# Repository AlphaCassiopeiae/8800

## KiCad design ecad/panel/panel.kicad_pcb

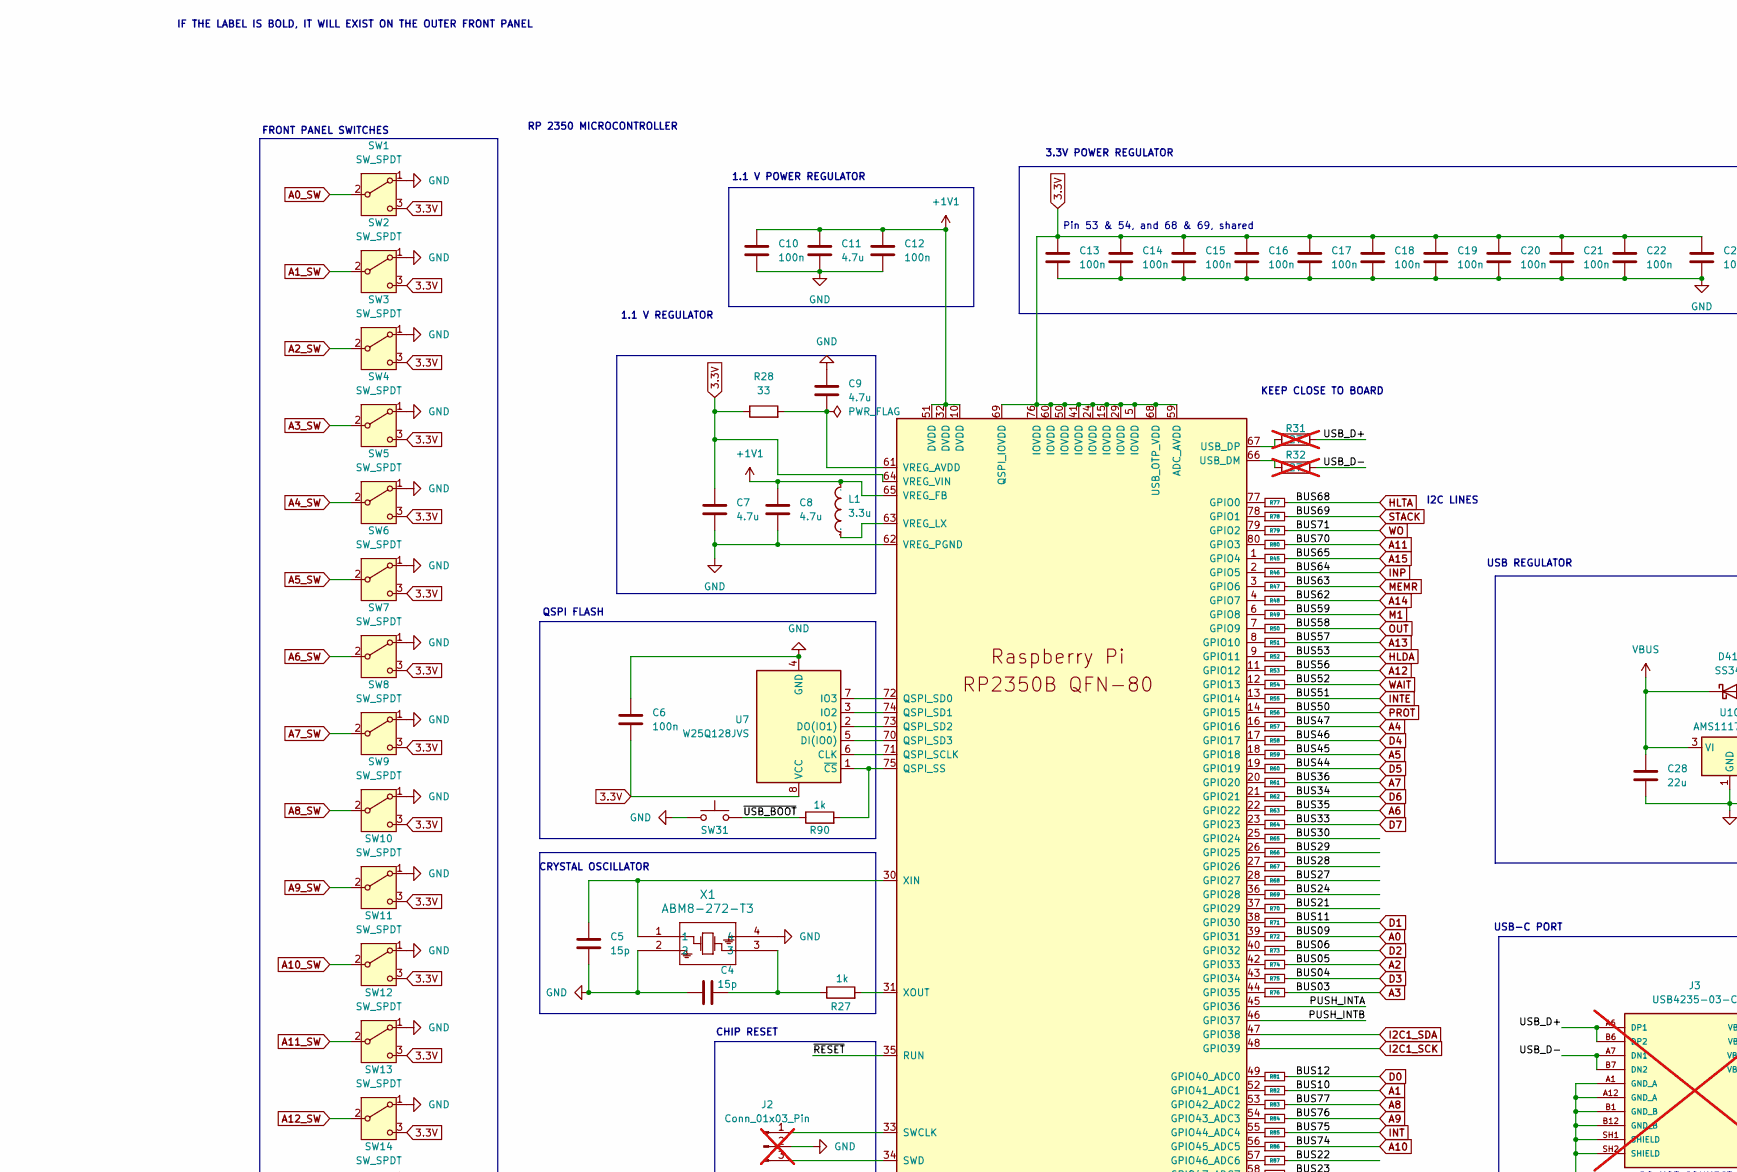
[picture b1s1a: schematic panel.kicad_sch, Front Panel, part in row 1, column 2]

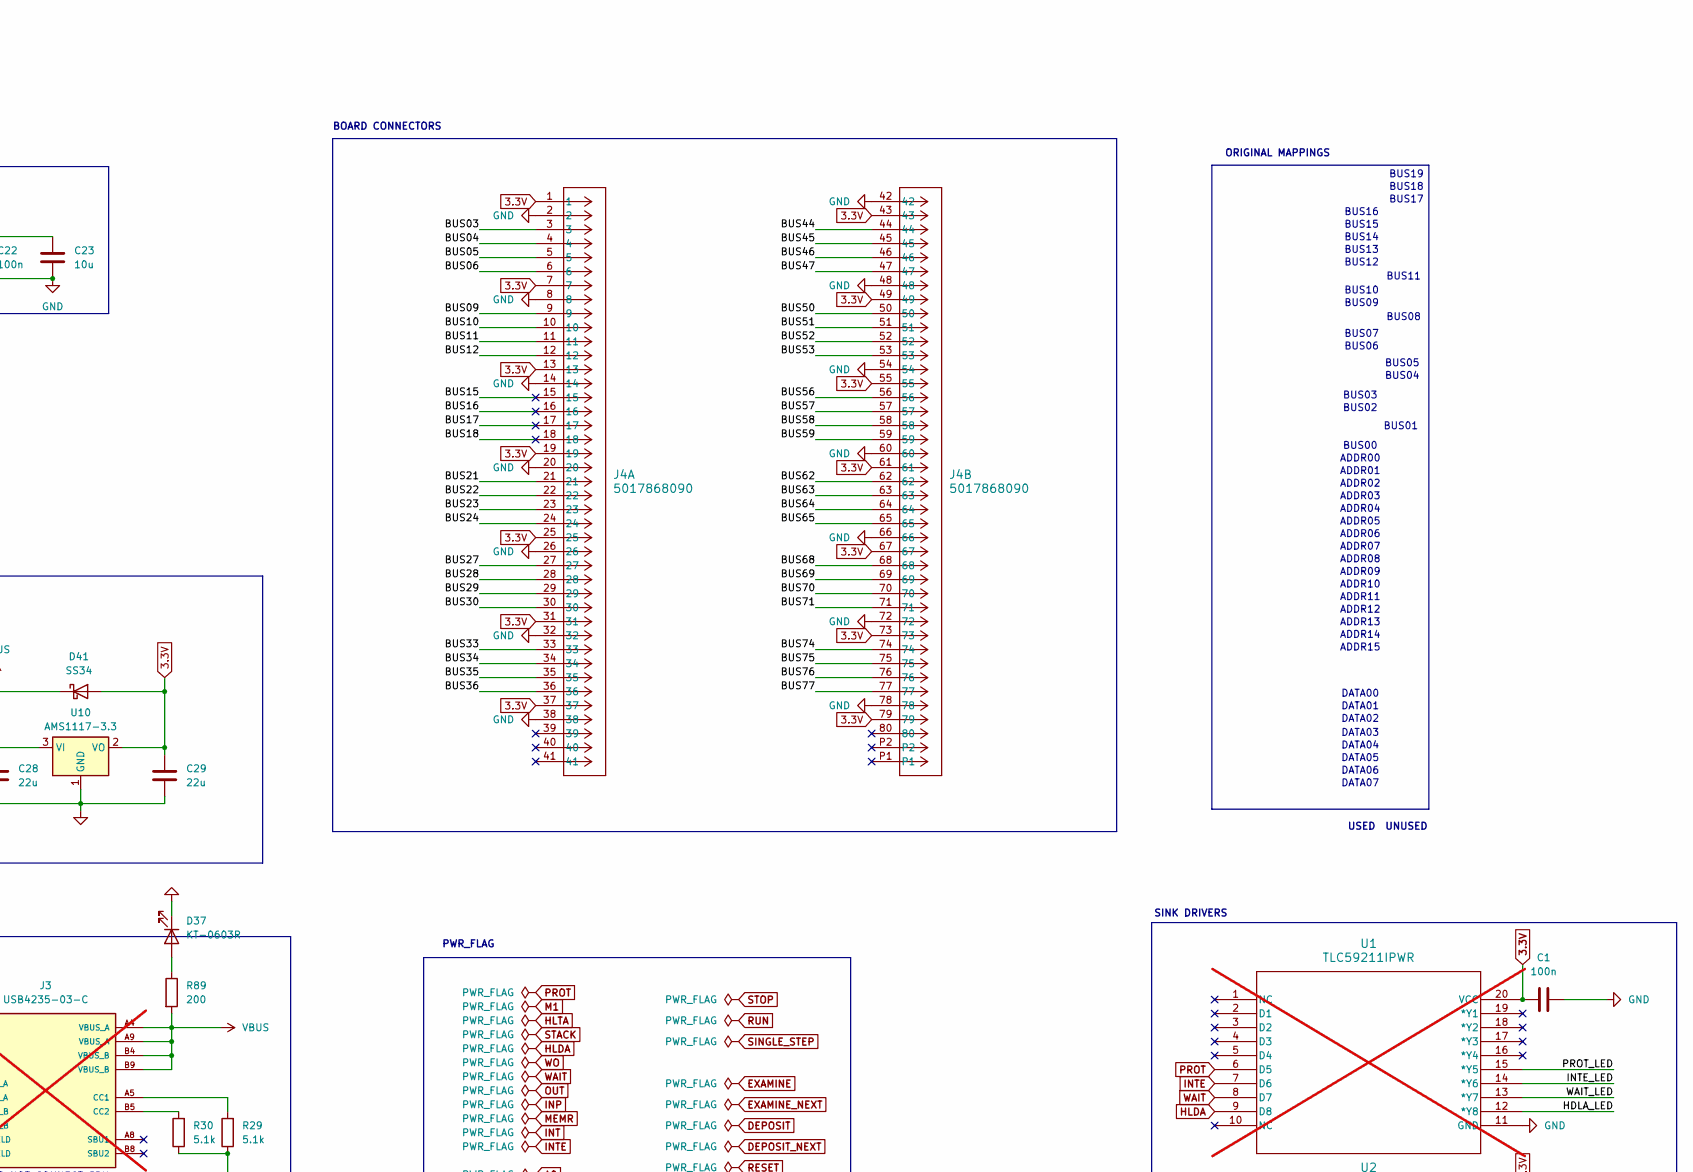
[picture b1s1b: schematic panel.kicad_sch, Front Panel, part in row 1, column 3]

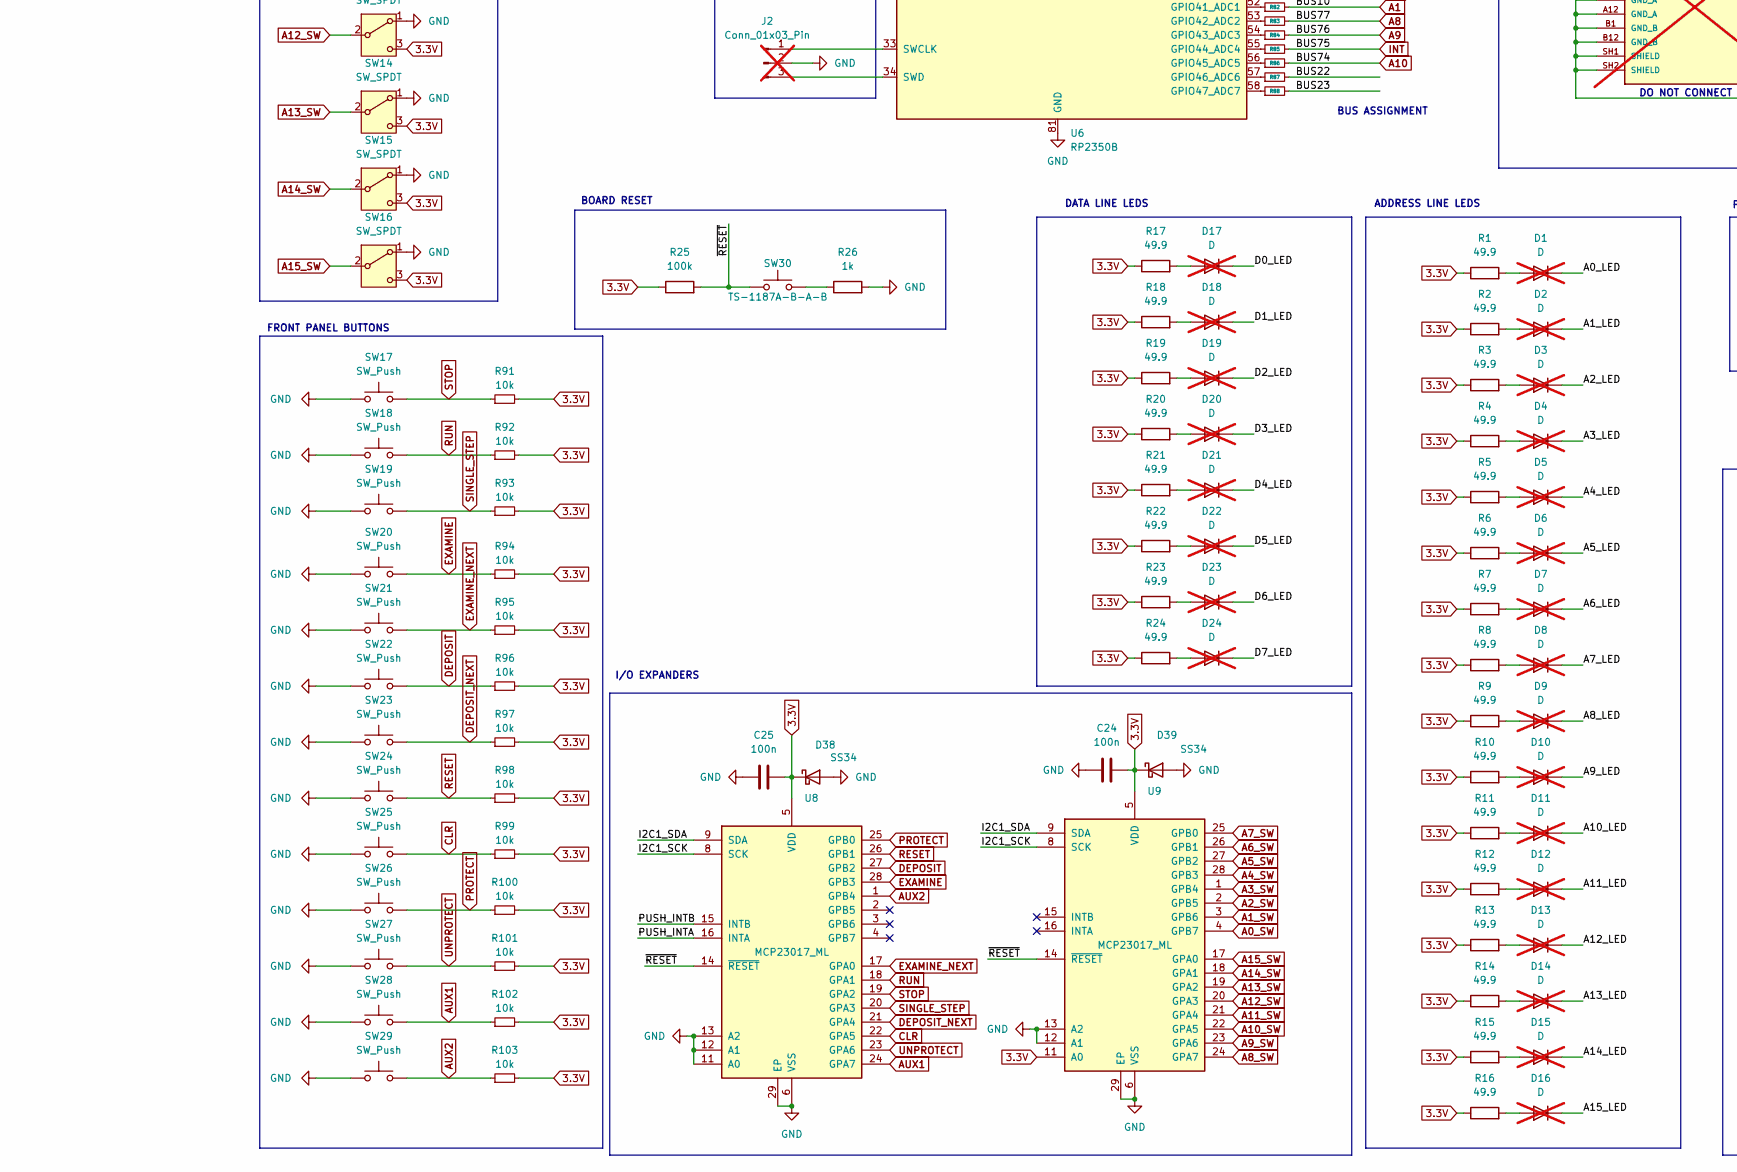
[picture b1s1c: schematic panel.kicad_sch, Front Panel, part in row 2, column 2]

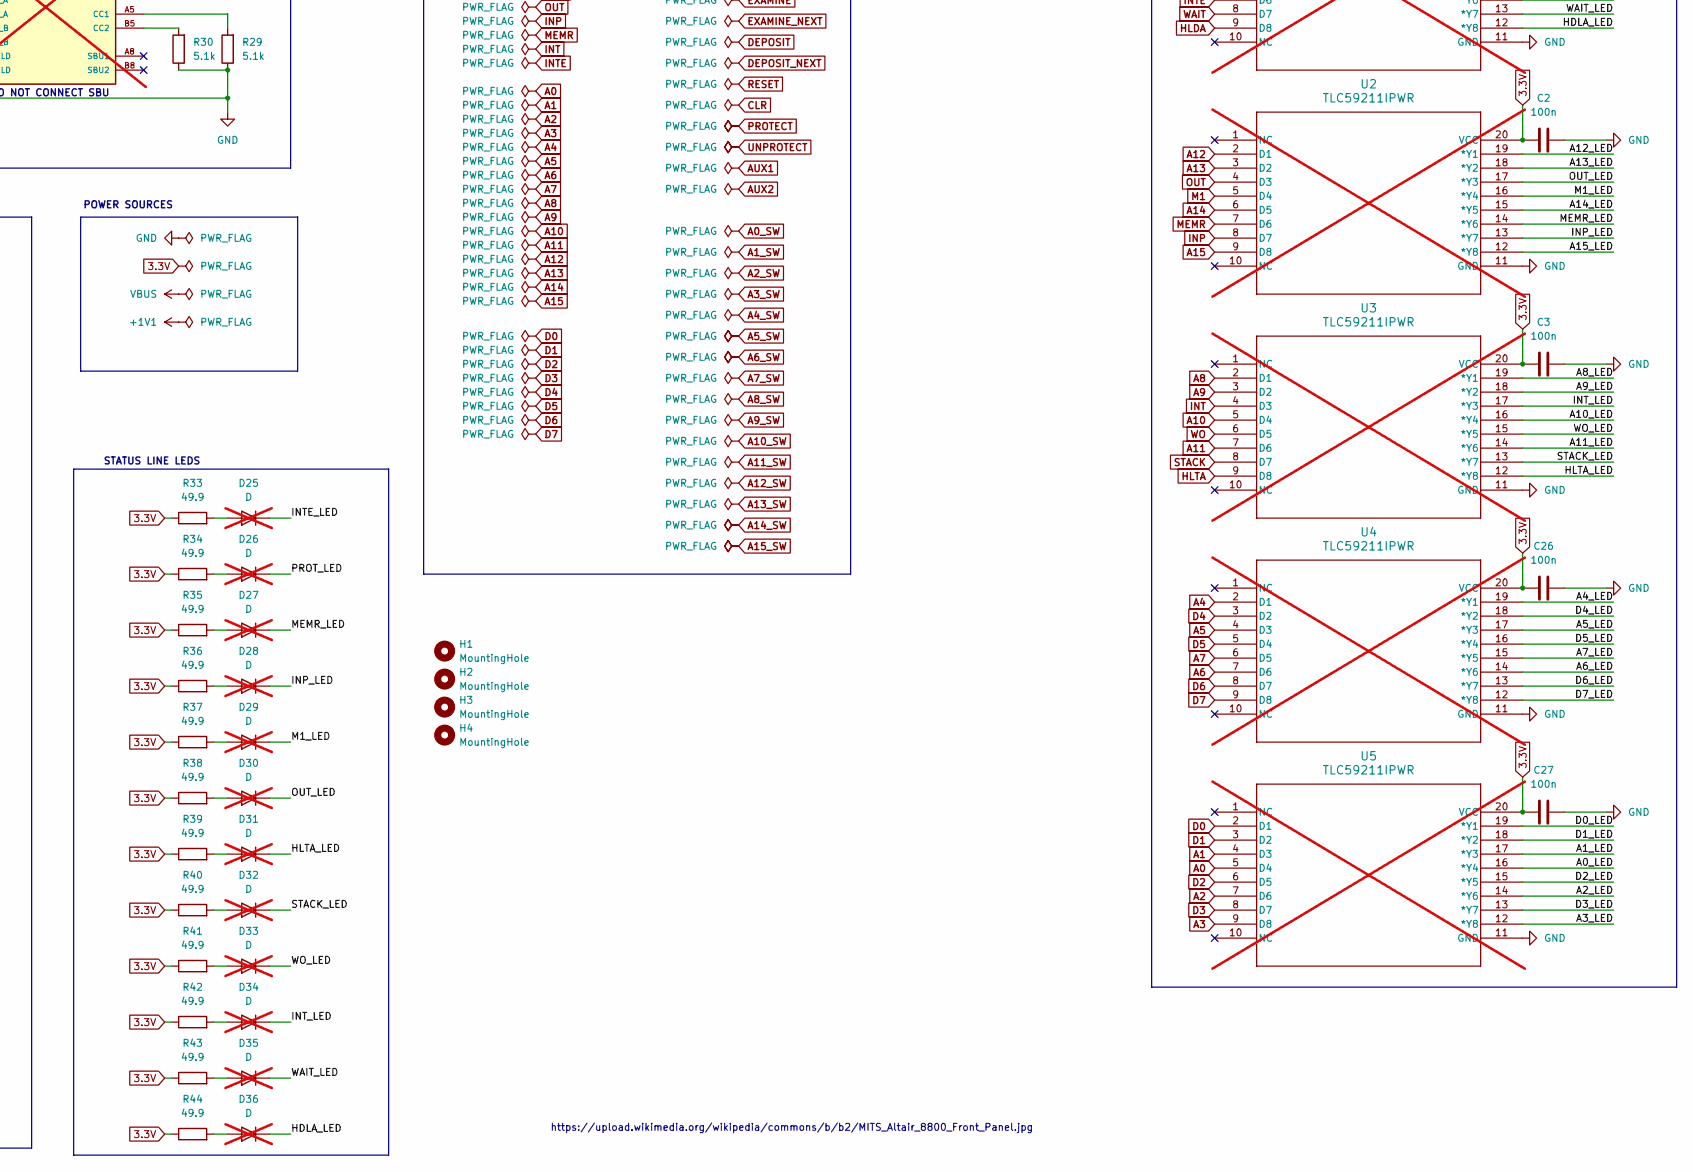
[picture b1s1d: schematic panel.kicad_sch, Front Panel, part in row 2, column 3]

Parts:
C1, C2, C3, C6, C10, C12, C13, C14, C15, C16, C17, C18, C19, C20, C21, C22, C24, C25, C26, C27: 100n; C_0402_1005Metric
C4, C5: 15p; C_0402_1005Metric
C7, C8, C9, C11: 4.7u; C_0402_1005Metric
C23: 10u; C_0402_1005Metric
C28, C29: 22u; C_1206_3216Metric
D1, D2, D3, D4, D5, D6, D7, D8, D9, D10, D11, D12, D13, D14, D15, D16, D17, D18, D19, D20, D21, D22, D23, D24, D25, D26, D27, D28, D29, D30, D31, D32, D33, D34, D35, D36: D; AA3528SECKTJ309; not fitted
D37: KT-0603R; LED_0603_1608Metric_Pad1.05x0.95mm_HandSolder; LCSC Part # C2286
D38, D39, D41: SS34; D_SMA
H1, H2, H3, H4: MountingHole; MountingHole_3.5mm
J2: Conn_01x03_Pin; JST_XH_B3B-XH-A_1x03_P2.50mm_Vertical; not fitted
J3: USB4235-03-C; GCT_USB4235-03-C_REVA; PARTREV A; not fitted
J4: 5017868090; CON_5017868090
L1: 3.3u; IND-SMD_L2.0-W1.6_AOTA-B201610S3R3-101-T; Manufacturer Part AOTA-B201610S3R3-101-T; LCSC Part # C42411119
R1, R2, R3, R4, R5, R6, R7, R8, R9, R10, R11, R12, R13, R14, R15, R16, R17, R18, R19, R20, R21, R22, R23, R24, R33, R34, R35, R36, R37, R38, R39, R40, R41, R42, R43, R44: 49.9; R_0402_1005Metric_Pad0.72x0.64mm_HandSolder
R25: 100k; R_0402_1005Metric_Pad0.72x0.64mm_HandSolder
R26, R27, R90: 1k; R_0402_1005Metric_Pad0.72x0.64mm_HandSolder
R28: 33; R_0402_1005Metric_Pad0.72x0.64mm_HandSolder
R29, R30: 5.1k; R_0402_1005Metric_Pad0.72x0.64mm_HandSolder
R31, R32: 27; R_0603_1608Metric_Pad0.98x0.95mm_HandSolder; not fitted
R45, R46, R47, R48, R49, R50, R51, R52, R53, R54, R55, R56, R57, R58, R59, R60, R61, R62, R63, R64, R65, R66, R67, R68, R69, R70, R71, R72, R73, R74, R75, R76, R77, R78, R79, R80, R81, R82, R83, R84, R85, R86, R87, R88: 330; R_0402_1005Metric_Pad0.72x0.64mm_HandSolder
R89: 200; R_0402_1005Metric_Pad0.72x0.64mm_HandSolder
R91, R92, R93, R94, R95, R96, R97, R98, R99, R100, R101, R102, R103: 10k; C_0402_1005Metric
SW1, SW2, SW3, SW4, SW5, SW6, SW7, SW8, SW9, SW10, SW11, SW12, SW13, SW14, SW15, SW16: SW_SPDT; SW_OS102011MS2QN1
SW17, SW18, SW19, SW20, SW21, SW22, SW23, SW24, SW25, SW26, SW27, SW28, SW29: SW_Push; SW_1825910-6-4
SW30, SW31: TS-1187A-B-A-B; SW_Push_1P1T_XKB_TS-1187A
U1, U2, U3, U4, U5: TLC59211IPWR; Texas_PWP0020A; not fitted
U6: RP2350B; RP2350-QFN-80-1EP_10x10_P0.4mm_EP3.4x3.4mm_ThermalVias
U7: W25Q128JVS; SOIC-8_5.23x5.23mm_P1.27mm
U8, U9: MCP23017_ML; QFN-28-1EP_6x6mm_P0.65mm_EP4.25x4.25mm; LCSC Part # C639770
U10: AMS1117-3.3; SOT-223-3_TabPin2
X1: ABM8-272-T3; ABM8-272-T3_ABR

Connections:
3.3V: C1.1, C2.1, C3.1, C6.1, C7.1, C13.1, C14.1, C15.1, C16.1, C17.1, C18.1, C19.1, C20.1, C21.1, C22.1, C23.1, C24.2, C25.2, C26.1, C27.1, C29.1, D38.1 (K), D39.1 (K), D41.2 (A), J4.1, J4.7, J4.13, J4.19, J4.25, J4.31, J4.37, J4.43, J4.49, J4.55, J4.61, J4.67, J4.73, J4.79, R1.1, R2.1, R3.1, R4.1, R5.1, R6.1, R7.1, R8.1, R9.1, R10.1, R11.1, R12.1, R13.1, R14.1, R15.1, R16.1, R17.1, R18.1, R19.1, R20.1, R21.1, R22.1, R23.1, R24.1, R25.1, R28.1, R33.1, R34.1, R35.1, R36.1, R37.1, R38.1, R39.1, R40.1, R41.1, R42.1, R43.1, R44.1, R91.2, R92.2, R93.2, R94.2, R95.2, R96.2, R97.2, R98.2, R99.2, R100.2, R101.2, R102.2, R103.2, SW1.3 (C), SW2.3 (C), SW3.3 (C), SW4.3 (C), SW5.3 (C), SW6.3 (C), SW7.3 (C), SW8.3 (C), SW9.3 (C), SW10.3 (C), SW11.3 (C), SW12.3 (C), SW13.3 (C), SW14.3 (C), SW15.3 (C), SW16.3 (C), U1.20 (VCC), U2.20 (VCC), U3.20 (VCC), U4.20 (VCC), U5.20 (VCC), U6.5 (IOVDD), U6.15 (IOVDD), U6.24 (IOVDD), U6.29 (IOVDD), U6.41 (IOVDD), U6.50 (IOVDD), U6.59 (ADC_AVDD), U6.60 (IOVDD), U6.64 (VREG_VIN), U6.68 (USB_OTP_VDD), U6.69 (QSPI_IOVDD), U6.76 (IOVDD), U7.8 (VCC), U8.5 (VDD), U9.5 (VDD), U9.11 (A0), U10.2 (VO)
+1V1: C8.1, C10.1, C11.1, C12.1, L1.2, U6.10 (DVDD), U6.32 (DVDD), U6.51 (DVDD), U6.65 (VREG_FB)
/A0_LED: D1.1 (K), U5.16 (*Y4)
/A1_LED: D2.1 (K), U5.17 (*Y3)
/A2_LED: D3.1 (K), U5.14 (*Y6)
/A3_LED: D4.1 (K), U5.12 (*Y8)
/A4_LED: D5.1 (K), U4.19 (*Y1)
/A5_LED: D6.1 (K), U4.17 (*Y3)
/A6_LED: D7.1 (K), U4.14 (*Y6)
/A7_LED: D8.1 (K), U4.15 (*Y5)
/A8_LED: D9.1 (K), U3.19 (*Y1)
/A9_LED: D10.1 (K), U3.18 (*Y2)
/A10_LED: D11.1 (K), U3.16 (*Y4)
/A11_LED: D12.1 (K), U3.14 (*Y6)
/A12_LED: D13.1 (K), U2.19 (*Y1)
/A13_LED: D14.1 (K), U2.18 (*Y2)
/A14_LED: D15.1 (K), U2.15 (*Y5)
/A15_LED: D16.1 (K), U2.12 (*Y8)
/BUS15: J4.15
/BUS16: J4.16
/BUS17: J4.17
/BUS18: J4.18
/BUS21: J4.21, R70.2
/BUS22: J4.22, R87.2
/BUS23: J4.23, R88.2
/BUS24: J4.24, R69.2
/BUS27: J4.27, R68.2
/BUS28: J4.28, R67.2
/BUS29: J4.29, R66.2
/BUS30: J4.30, R65.2
/D0_LED: D17.1 (K), U5.19 (*Y1)
/D1_LED: D18.1 (K), U5.18 (*Y2)
/D2_LED: D19.1 (K), U5.15 (*Y5)
/D3_LED: D20.1 (K), U5.13 (*Y7)
/D4_LED: D21.1 (K), U4.18 (*Y2)
/D5_LED: D22.1 (K), U4.16 (*Y4)
/D6_LED: D23.1 (K), U4.13 (*Y7)
/D7_LED: D24.1 (K), U4.12 (*Y8)
/HDLA_LED: D36.1 (K), U1.12 (*Y8)
/HLTA_LED: D31.1 (K), U3.12 (*Y8)
/INP_LED: D28.1 (K), U2.13 (*Y7)
/INTE_LED: D25.1 (K), U1.14 (*Y6)
/INT_LED: D34.1 (K), U3.17 (*Y3)
/M1_LED: D29.1 (K), U2.16 (*Y4)
/MEMR_LED: D27.1 (K), U2.14 (*Y6)
/OUT_LED: D30.1 (K), U2.17 (*Y3)
/PROT_LED: D26.1 (K), U1.15 (*Y5)
/PUSH_INTA: U6.45 (GPIO36), U8.16 (INTA)
/PUSH_INTB: U6.46 (GPIO37), U8.15 (INTB)
/STACK_LED: D32.1 (K), U3.13 (*Y7)
/USB_D+: J3.A6 (DP1), J3.B6 (DP2), R31.2
/USB_D-: J3.A7 (DN1), J3.B7 (DN2), R32.2
/WAIT_LED: D35.1 (K), U1.13 (*Y7)
/WO_LED: D33.1 (K), U3.15 (*Y5)
/~RESET: R25.2, SW30.1, U6.35 (RUN), U8.14 (~RESET), U9.14 (~RESET)
/~USB_BOOT: R90.1, SW31.2
A0: J4.9, R72.2, U5.5 (D4)
A0_SW: SW1.2 (B), U9.4 (GPB7)
A1: J4.10, R82.2, U5.4 (D3)
A1_SW: SW2.2 (B), U9.3 (GPB6)
A2: J4.5, R74.2, U5.7 (D6)
A2_SW: SW3.2 (B), U9.2 (GPB5)
A3: J4.3, R76.2, U5.9 (D8)
A3_SW: SW4.2 (B), U9.1 (GPB4)
A4: J4.47, R57.2, U4.2 (D1)
A4_SW: SW5.2 (B), U9.28 (GPB3)
A5: J4.45, R59.2, U4.4 (D3)
A5_SW: SW6.2 (B), U9.27 (GPB2)
A6: J4.35, R63.2, U4.7 (D6)
A6_SW: SW7.2 (B), U9.26 (GPB1)
A7: J4.36, R61.2, U4.6 (D5)
A7_SW: SW8.2 (B), U9.25 (GPB0)
A8: J4.77, R83.2, U3.2 (D1)
A8_SW: SW9.2 (B), U9.24 (GPA7)
A9: J4.76, R84.2, U3.3 (D2)
A9_SW: SW10.2 (B), U9.23 (GPA6)
A10: J4.74, R86.2, U3.5 (D4)
A10_SW: SW11.2 (B), U9.22 (GPA5)
A11: J4.70, R80.2, U3.7 (D6)
A11_SW: SW12.2 (B), U9.21 (GPA4)
A12: J4.56, R53.2, U2.2 (D1)
A12_SW: SW13.2 (B), U9.20 (GPA3)
A13: J4.57, R51.2, U2.3 (D2)
A13_SW: SW14.2 (B), U9.19 (GPA2)
A14: J4.62, R48.2, U2.6 (D5)
A14_SW: SW15.2 (B), U9.18 (GPA1)
A15: J4.65, R45.2, U2.9 (D8)
A15_SW: SW16.2 (B), U9.17 (GPA0)
AUX1: R102.1, SW28.2, U8.24 (GPA7)
AUX2: R103.1, SW29.2, U8.1 (GPB4)
CLR: R99.1, SW25.2, U8.22 (GPA5)
D0: J4.12, R81.2, U5.2 (D1)
D1: J4.11, R71.2, U5.3 (D2)
D2: J4.6, R73.2, U5.6 (D5)
D3: J4.4, R75.2, U5.8 (D7)
D4: J4.46, R58.2, U4.3 (D2)
D5: J4.44, R60.2, U4.5 (D4)
D6: J4.34, R62.2, U4.8 (D7)
D7: J4.33, R64.2, U4.9 (D8)
DEPOSIT: R96.1, SW22.2, U8.27 (GPB2)
DEPOSIT_NEXT: R97.1, SW23.2, U8.21 (GPA4)
EXAMINE: R94.1, SW20.2, U8.28 (GPB3)
EXAMINE_NEXT: R95.1, SW21.2, U8.17 (GPA0)
GND: C1.2, C2.2, C3.2, C4.2, C5.2, C6.2, C7.2, C8.2, C9.1, C10.2, C11.2, C12.2, C13.2, C14.2, C15.2, C16.2, C17.2, C18.2, C19.2, C20.2, C21.2, C22.2, C23.2, C24.1, C25.1, C26.2, C27.2, C28.2, C29.2, D37.1 (K), D38.2 (A), D39.2 (A), J2.2, J3.A1 (GND_A), J3.A12 (GND_A), J3.B1 (GND_B), J3.B12 (GND_B), J3.SH1 (SHIELD), J3.SH2 (SHIELD), J4.2, J4.8, J4.14, J4.20, J4.26, J4.32, J4.38, J4.42, J4.48, J4.54, J4.60, J4.66, J4.72, J4.78, R26.2, R29.1, R30.1, SW1.1 (A), SW2.1 (A), SW3.1 (A), SW4.1 (A), SW5.1 (A), SW6.1 (A), SW7.1 (A), SW8.1 (A), SW9.1 (A), SW10.1 (A), SW11.1 (A), SW12.1 (A), SW13.1 (A), SW14.1 (A), SW15.1 (A), SW16.1 (A), SW17.1, SW18.1, SW19.1, SW20.1, SW21.1, SW22.1, SW23.1, SW24.1, SW25.1, SW26.1, SW27.1, SW28.1, SW29.1, SW31.1, U1.11 (GND), U2.11 (GND), U3.11 (GND), U4.11 (GND), U5.11 (GND), U6.62 (VREG_PGND), U6.81 (GND), U7.4 (GND), U8.6 (VSS), U8.11 (A0), U8.12 (A1), U8.13 (A2), U8.29 (EP), U9.6 (VSS), U9.12 (A1), U9.13 (A2), U9.29 (EP), U10.1 (GND), X1.2, X1.4
HLDA: J4.53, R52.2, U1.9 (D8)
HLTA: J4.68, R77.2, U3.9 (D8)
I2C1_SCK: U6.48 (GPIO39), U8.8 (SCK), U9.8 (SCK)
I2C1_SDA: U6.47 (GPIO38), U8.9 (SDA), U9.9 (SDA)
INP: J4.64, R46.2, U2.8 (D7)
INT: J4.75, R85.2, U3.4 (D3)
INTE: J4.51, R55.2, U1.7 (D6)
M1: J4.59, R49.2, U2.5 (D4)
MEMR: J4.63, R47.2, U2.7 (D6)
unnamed: C4.1, R27.1, X1.3
unnamed: D1.2 (A), R1.2
unnamed: D2.2 (A), R2.2
unnamed: D3.2 (A), R3.2
unnamed: D4.2 (A), R4.2
unnamed: D5.2 (A), R5.2
unnamed: D6.2 (A), R6.2
unnamed: D7.2 (A), R7.2
unnamed: D8.2 (A), R8.2
unnamed: D9.2 (A), R9.2
unnamed: D10.2 (A), R10.2
unnamed: D11.2 (A), R11.2
unnamed: D12.2 (A), R12.2
unnamed: D13.2 (A), R13.2
unnamed: D14.2 (A), R14.2
unnamed: D15.2 (A), R15.2
unnamed: D16.2 (A), R16.2
unnamed: D17.2 (A), R17.2
unnamed: D18.2 (A), R18.2
unnamed: D19.2 (A), R19.2
unnamed: D20.2 (A), R20.2
unnamed: D21.2 (A), R21.2
unnamed: D22.2 (A), R22.2
unnamed: D23.2 (A), R23.2
unnamed: D24.2 (A), R24.2
unnamed: D25.2 (A), R33.2
unnamed: D26.2 (A), R34.2
unnamed: D27.2 (A), R35.2
unnamed: D28.2 (A), R36.2
unnamed: D29.2 (A), R37.2
unnamed: D30.2 (A), R38.2
unnamed: D31.2 (A), R39.2
unnamed: D32.2 (A), R40.2
unnamed: D33.2 (A), R41.2
unnamed: D34.2 (A), R42.2
unnamed: D35.2 (A), R43.2
unnamed: D36.2 (A), R44.2
unnamed: D37.2 (A), R89.1
unnamed: J2.1, U6.33 (SWCLK)
unnamed: J2.3, U6.34 (SWD)
unnamed: J3.A5 (CC1), R29.2
unnamed: J3.B5 (CC2), R30.2
unnamed: R26.1, SW30.2
unnamed: R77.1, U6.77 (GPIO0)
unnamed: R78.1, U6.78 (GPIO1)
unnamed: R79.1, U6.79 (GPIO2)
unnamed: R80.1, U6.80 (GPIO3)
unnamed: R45.1, U6.1 (GPIO4)
unnamed: R46.1, U6.2 (GPIO5)
unnamed: R47.1, U6.3 (GPIO6)
unnamed: R48.1, U6.4 (GPIO7)
unnamed: R49.1, U6.6 (GPIO8)
unnamed: R50.1, U6.7 (GPIO9)
unnamed: R51.1, U6.8 (GPIO10)
unnamed: R52.1, U6.9 (GPIO11)
unnamed: R53.1, U6.11 (GPIO12)
unnamed: R54.1, U6.12 (GPIO13)
unnamed: R55.1, U6.13 (GPIO14)
unnamed: R56.1, U6.14 (GPIO15)
unnamed: R57.1, U6.16 (GPIO16)
unnamed: R58.1, U6.17 (GPIO17)
unnamed: R59.1, U6.18 (GPIO18)
unnamed: R60.1, U6.19 (GPIO19)
unnamed: R61.1, U6.20 (GPIO20)
unnamed: R62.1, U6.21 (GPIO21)
unnamed: R63.1, U6.22 (GPIO22)
unnamed: R64.1, U6.23 (GPIO23)
unnamed: R65.1, U6.25 (GPIO24)
unnamed: R66.1, U6.26 (GPIO25)
unnamed: R67.1, U6.27 (GPIO26)
unnamed: R68.1, U6.28 (GPIO27)
unnamed: R69.1, U6.36 (GPIO28)
unnamed: R70.1, U6.37 (GPIO29)
unnamed: R71.1, U6.38 (GPIO30)
unnamed: R72.1, U6.39 (GPIO31)
unnamed: R73.1, U6.40 (GPIO32)
unnamed: R74.1, U6.42 (GPIO33)
unnamed: R75.1, U6.43 (GPIO34)
unnamed: R76.1, U6.44 (GPIO35)
unnamed: R81.1, U6.49 (GPIO40_ADC0)
unnamed: R82.1, U6.52 (GPIO41_ADC1)
unnamed: R83.1, U6.53 (GPIO42_ADC2)
unnamed: R84.1, U6.54 (GPIO43_ADC3)
unnamed: R85.1, U6.55 (GPIO44_ADC4)
unnamed: R86.1, U6.56 (GPIO45_ADC5)
unnamed: R87.1, U6.57 (GPIO46_ADC6)
unnamed: R88.1, U6.58 (GPIO47_ADC7)
unnamed: U6.71 (QSPI_SCLK), U7.6 (CLK)
unnamed: U6.72 (QSPI_SD0), U7.7 (IO3)
unnamed: U6.74 (QSPI_SD1), U7.3 (IO2)
unnamed: U6.73 (QSPI_SD2), U7.2 (DO(IO1))
unnamed: U6.70 (QSPI_SD3), U7.5 (DI(IO0))
unnamed: R90.2, U6.75 (QSPI_SS), U7.1 (~CS)
unnamed: R32.1, U6.66 (USB_DM)
unnamed: R31.1, U6.67 (USB_DP)
unnamed: C9.2, R28.2, U6.61 (VREG_AVDD)
unnamed: L1.1, U6.63 (VREG_LX)
unnamed: C5.1, U6.30 (XIN), X1.1
unnamed: R27.2, U6.31 (XOUT)
OUT: J4.58, R50.2, U2.4 (D3)
PROT: J4.50, R56.2, U1.6 (D5)
PROTECT: R100.1, SW26.2, U8.25 (GPB0)
RESET: R98.1, SW24.2, U8.26 (GPB1)
RUN: R92.1, SW18.2, U8.18 (GPA1)
SINGLE_STEP: R93.1, SW19.2, U8.20 (GPA3)
STACK: J4.69, R78.2, U3.8 (D7)
STOP: R91.1, SW17.2, U8.19 (GPA2)
UNPROTECT: R101.1, SW27.2, U8.23 (GPA6)
VBUS: C28.1, D41.1 (K), J3.A4 (VBUS_A), J3.A9 (VBUS_A), J3.B4 (VBUS_B), J3.B9 (VBUS_B), R89.2, U10.3 (VI)
WAIT: J4.52, R54.2, U1.8 (D7)
WO: J4.71, R79.2, U3.6 (D5)

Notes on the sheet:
ADDR02
BUS09
ADDR08
CRYSTAL OSCILLATOR
BUS10
POWER SOURCES
I/O EXPANDERS
ADDR03
RP 2350 MICROCONTROLLER
IF THE LABEL IS BOLD, IT WILL EXIST ON THE OUTER FRONT PANEL
BUS18
BUS11
BUS17
ADDR06
BUS19
BUS01
DATA00
I2C LINES
DATA04
ADDR11
BUS06
1.1 V REGULATOR
DATA07
BUS03
SINK DRIVERS
BUS00
DATA06
FRONT PANEL SWITCHES
BOARD RESET
1.1 V POWER REGULATOR
QSPI FLASH
BUS02
BUS13
ADDR01
CHIP RESET
https://upload.wikimedia.org/wikipedia/commons/b/b2/MITS_Altair_8800_Front_Panel.jpg
BUS07
STATUS LINE LEDS
BUS08
DATA LINE LEDS

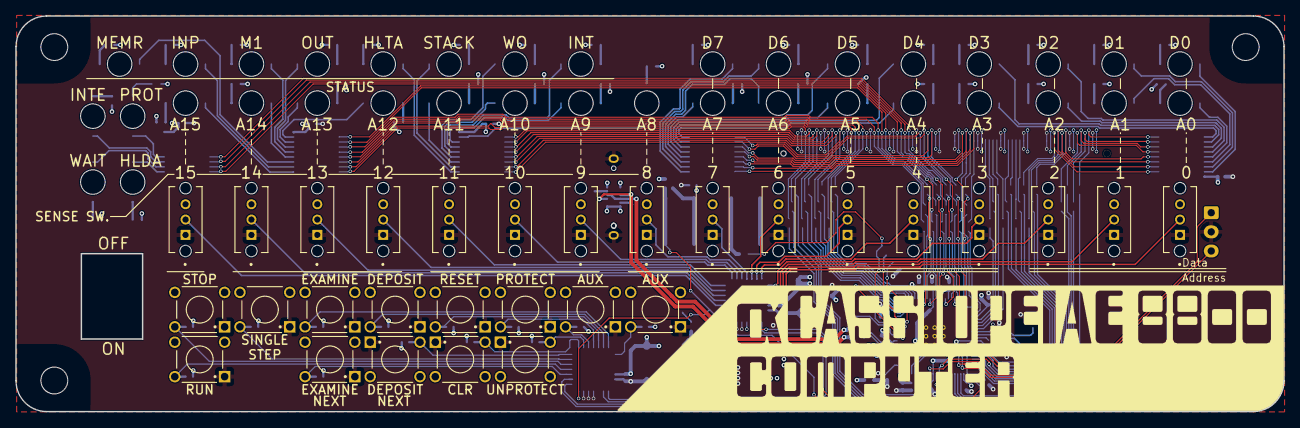
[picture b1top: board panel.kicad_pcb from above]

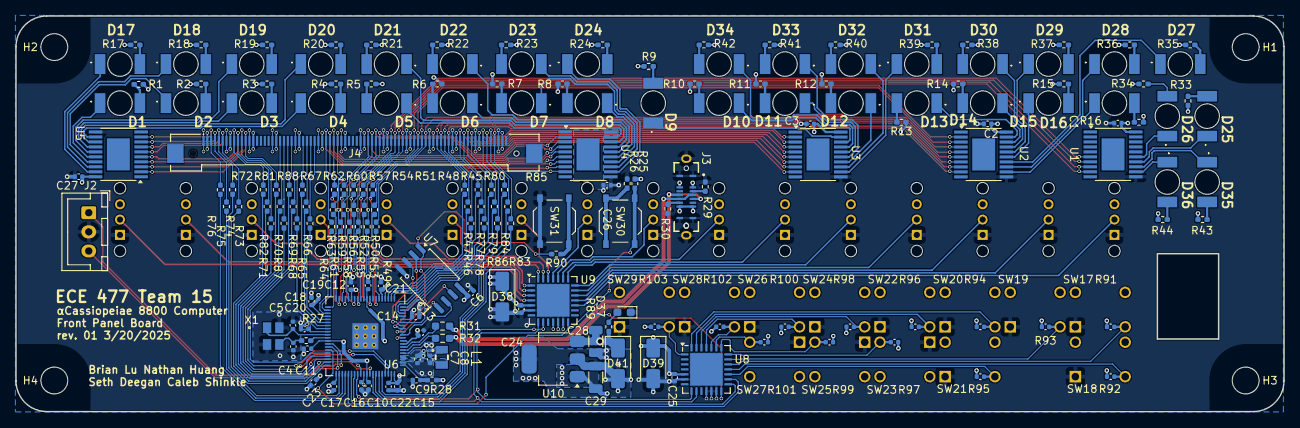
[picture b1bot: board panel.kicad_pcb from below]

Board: 4 copper layers, 165.5 x 51.6 mm, 222 parts (189 on the bottom side), 220 nets.
